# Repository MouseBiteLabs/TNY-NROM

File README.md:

# TNY-NROM
This is a custom NROM board for the TinyTendo handheld console by <a href="https://github.com/Redherring32">Redherring32</a>. This board replicates <a href="https://www.nesdev.org/wiki/NROM">standard NROM NES boards</a> - the simplest board type, used for many of the earliest NES games like Duck Hunt, Balloon Fight, and one of the most popular NES games that created millions of gamers and cemented Nintendo as a top-tier video game company for decades to come... <a href="https://nescartdb.com/profile/view/1076/chubby-cherub">Chubby Cherub</a>!

NROM games support up to 32 KB space for the PRG ROM and up to 8 KB for the CHR ROM. Since these boards use the 39SF040 for both, you should use FamiROM or some other utility to duplicate the ROM files to completely fill up the entire space on the Flash chip.

<a href="https://www.infiniteneslives.com/inlretro.php">You can use INL's programmer to load the PRG and CHR ROMs.</a>

# Board Characteristics

- Thickness: 1.6 mm
- Surface Finish: ENIG
- Chamfered edges (45°)

# Bill of Materials

Capacitors should be at least 16V rated.

| Reference Designator  | Part Number/Value | Footprint  |
| ------------- | ------------- | ------------- |
| U2  | <a href="https://www.mouser.com/ProductDetail/Microchip-Technology/SST39SF040-70-4C-WHE?qs=Oo69DRhzroe%2FJKrgAmUE5Q%3D%3D">39SF040</a>  | TSOP32  |
| U3  | <a href="https://www.mouser.com/ProductDetail/Microchip-Technology/SST39SF040-70-4C-WHE?qs=Oo69DRhzroe%2FJKrgAmUE5Q%3D%3D">39SF040</a>  | TSOP32  |
| C1  | 22 uF (tantalum) | 1206  |
| C2  | 100 nF (ceramic) | 0603  |
| C3  | 100 nF (ceramic) | 0603  |
| R1  | 47 kΩ | 0603  |

# H/V Pads

NROM games usually will have H and V pads on the PCB, you can find the original game in <a href="https://nescartdb.com/">NESCartDB</a> to find out which you should solder. FamiROM should also tell you as well - bridge the middle pad to the left for Vertical mirroring (H), bridge to the right for Horizontal mirroring (V). Yes, it is "backwards" but <a href="https://www.youtube.com/watch?v=UepNwgFJ83k&ab_channel=DisplacedGamers">there is a reason for it</a>.

# Revision History

## TNY-NROM-02

- Updated cart edge pinout
- Flipped location of PRG and CHR chips
- Changed footprint of PRG and CHR to slimmer TSOP32 package as defined in the datasheet
- Add keyhole in middle of board, off-center

## TNY-NROM-01

- Initial version

# License:
Licensed under the TAPR Open Hardware License (www.tapr.org/OHL)

©MouseBiteLabs 2022

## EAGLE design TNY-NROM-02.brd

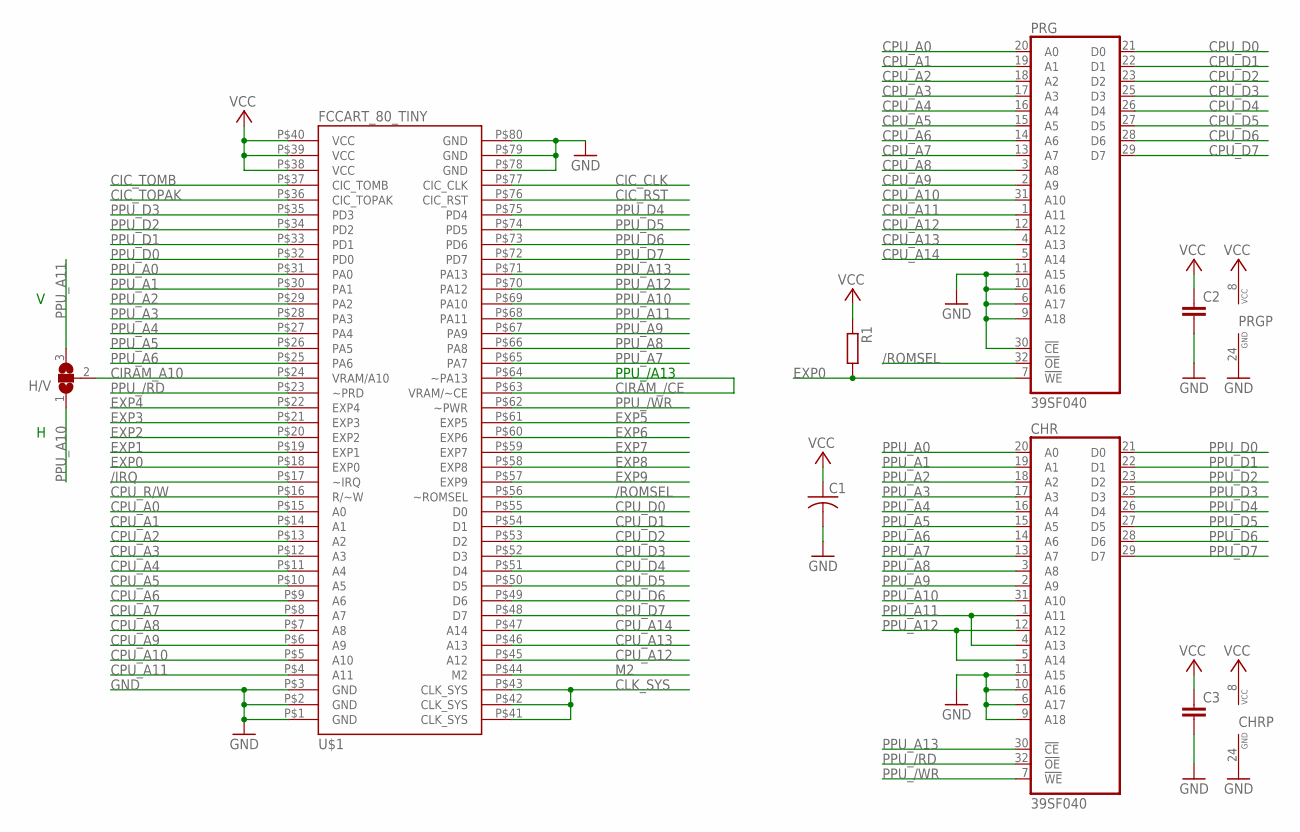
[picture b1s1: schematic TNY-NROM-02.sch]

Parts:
C1: C-USC1206; C1206
C2, C3: C-EUC0603K; C0603K
CHR: 39SF040; TSOP32_SHORT
H/V: SJ2W; SJ_2
PRG: 39SF040; TSOP32_SHORT
R1: RR0603; R0603
U$1: FCCART_80_TINY

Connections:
/IRQ: U$1.P$17 (~IRQ)
/ROMSEL: PRG.32 (!OE), U$1.P$56 (~ROMSEL)
CIC_CLK: U$1.P$77 (CIC_CLK)
CIC_RST: U$1.P$76 (CIC_RST)
CIC_TOMB: U$1.P$37 (CIC_TOMB)
CIC_TOPAK: U$1.P$36 (CIC_TOPAK)
CIRAM_/CE: U$1.P$63 (VRAM/~CE), U$1.P$64 (~PA13)
CIRAM_A10: H/V.2, U$1.P$24 (VRAM/A10)
CLK_SYS: U$1.P$41 (CLK_SYS), U$1.P$42 (CLK_SYS), U$1.P$43 (CLK_SYS)
CPU_A0: PRG.20 (A0), U$1.P$15 (A0)
CPU_A1: PRG.19 (A1), U$1.P$14 (A1)
CPU_A2: PRG.18 (A2), U$1.P$13 (A2)
CPU_A3: PRG.17 (A3), U$1.P$12 (A3)
CPU_A4: PRG.16 (A4), U$1.P$11 (A4)
CPU_A5: PRG.15 (A5), U$1.P$10 (A5)
CPU_A6: PRG.14 (A6), U$1.P$9 (A6)
CPU_A7: PRG.13 (A7), U$1.P$8 (A7)
CPU_A8: PRG.3 (A8), U$1.P$7 (A8)
CPU_A9: PRG.2 (A9), U$1.P$6 (A9)
CPU_A10: PRG.31 (A10), U$1.P$5 (A10)
CPU_A11: PRG.1 (A11), U$1.P$4 (A11)
CPU_A12: PRG.12 (A12), U$1.P$45 (A12)
CPU_A13: PRG.4 (A13), U$1.P$46 (A13)
CPU_A14: PRG.5 (A14), U$1.P$47 (A14)
CPU_D0: PRG.21 (D0), U$1.P$55 (D0)
CPU_D1: PRG.22 (D1), U$1.P$54 (D1)
CPU_D2: PRG.23 (D2), U$1.P$53 (D2)
CPU_D3: PRG.25 (D3), U$1.P$52 (D3)
CPU_D4: PRG.26 (D4), U$1.P$51 (D4)
CPU_D5: PRG.27 (D5), U$1.P$50 (D5)
CPU_D6: PRG.28 (D6), U$1.P$49 (D6)
CPU_D7: PRG.29 (D7), U$1.P$48 (D7)
CPU_R/W: U$1.P$16 (R/~W)
EXP0: PRG.7 (!WE), R1.2, U$1.P$18 (EXP0)
EXP1: U$1.P$19 (EXP1)
EXP2: U$1.P$20 (EXP2)
EXP3: U$1.P$21 (EXP3)
EXP4: U$1.P$22 (EXP4)
EXP5: U$1.P$61 (EXP5)
EXP6: U$1.P$60 (EXP6)
EXP7: U$1.P$59 (EXP7)
EXP8: U$1.P$58 (EXP8)
EXP9: U$1.P$57 (EXP9)
GND: C1.2, C2.2, C3.2, CHR.6 (A17), CHR.9 (A18), CHR.10 (A16), CHR.11 (A15), CHR.24 (GND), PRG.6 (A17), PRG.9 (A18), PRG.10 (A16), PRG.11 (A15), PRG.24 (GND), PRG.30 (!CE), U$1.P$1 (GND), U$1.P$2 (GND), U$1.P$3 (GND), U$1.P$78 (GND), U$1.P$79 (GND), U$1.P$80 (GND)
M2: U$1.P$44 (M2)
PPU_/RD: CHR.32 (!OE), U$1.P$23 (~PRD)
PPU_/WR: CHR.7 (!WE), U$1.P$62 (~PWR)
PPU_A0: CHR.20 (A0), U$1.P$31 (PA0)
PPU_A1: CHR.19 (A1), U$1.P$30 (PA1)
PPU_A2: CHR.18 (A2), U$1.P$29 (PA2)
PPU_A3: CHR.17 (A3), U$1.P$28 (PA3)
PPU_A4: CHR.16 (A4), U$1.P$27 (PA4)
PPU_A5: CHR.15 (A5), U$1.P$26 (PA5)
PPU_A6: CHR.14 (A6), U$1.P$25 (PA6)
PPU_A7: CHR.13 (A7), U$1.P$65 (PA7)
PPU_A8: CHR.3 (A8), U$1.P$66 (PA8)
PPU_A9: CHR.2 (A9), U$1.P$67 (PA9)
PPU_A10: CHR.31 (A10), H/V.1, U$1.P$69 (PA10)
PPU_A11: CHR.1 (A11), CHR.4 (A13), H/V.3, U$1.P$68 (PA11)
PPU_A12: CHR.5 (A14), CHR.12 (A12), U$1.P$70 (PA12)
PPU_A13: CHR.30 (!CE), U$1.P$71 (PA13)
PPU_D0: CHR.21 (D0), U$1.P$32 (PD0)
PPU_D1: CHR.22 (D1), U$1.P$33 (PD1)
PPU_D2: CHR.23 (D2), U$1.P$34 (PD2)
PPU_D3: CHR.25 (D3), U$1.P$35 (PD3)
PPU_D4: CHR.26 (D4), U$1.P$75 (PD4)
PPU_D5: CHR.27 (D5), U$1.P$74 (PD5)
PPU_D6: CHR.28 (D6), U$1.P$73 (PD6)
PPU_D7: CHR.29 (D7), U$1.P$72 (PD7)
VCC: C1.1, C2.1, C3.1, CHR.8 (VCC), PRG.8 (VCC), R1.1, U$1.P$38 (VCC), U$1.P$39 (VCC), U$1.P$40 (VCC)

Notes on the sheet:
PPU_/A13

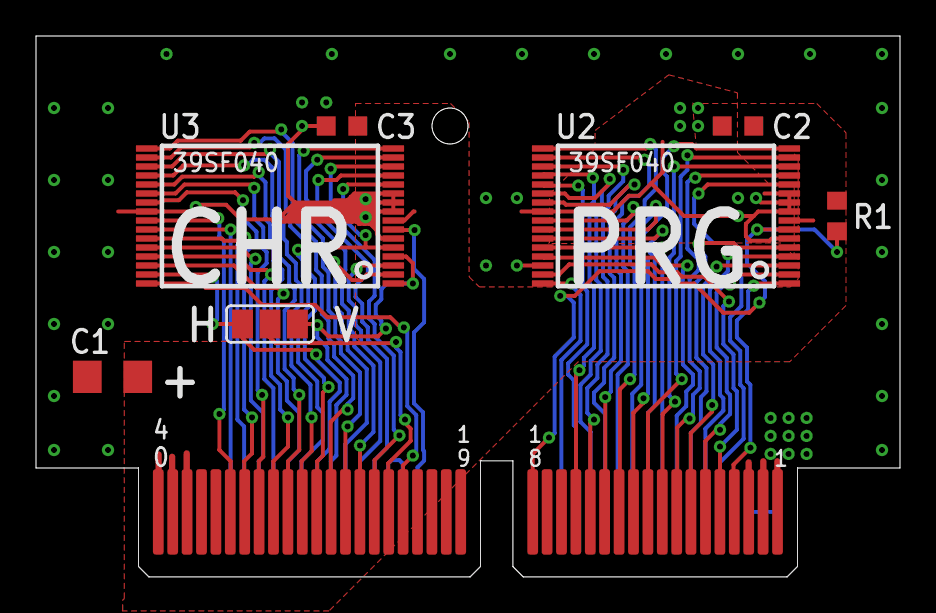
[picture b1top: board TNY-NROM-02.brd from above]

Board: 2 copper layers, 48.0 x 30.1 mm, 8 parts (0 on the bottom side), 54 nets.

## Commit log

2022-05-26 Create LICENSE
2022-05-26 Upload schematic/board files and gerbers
